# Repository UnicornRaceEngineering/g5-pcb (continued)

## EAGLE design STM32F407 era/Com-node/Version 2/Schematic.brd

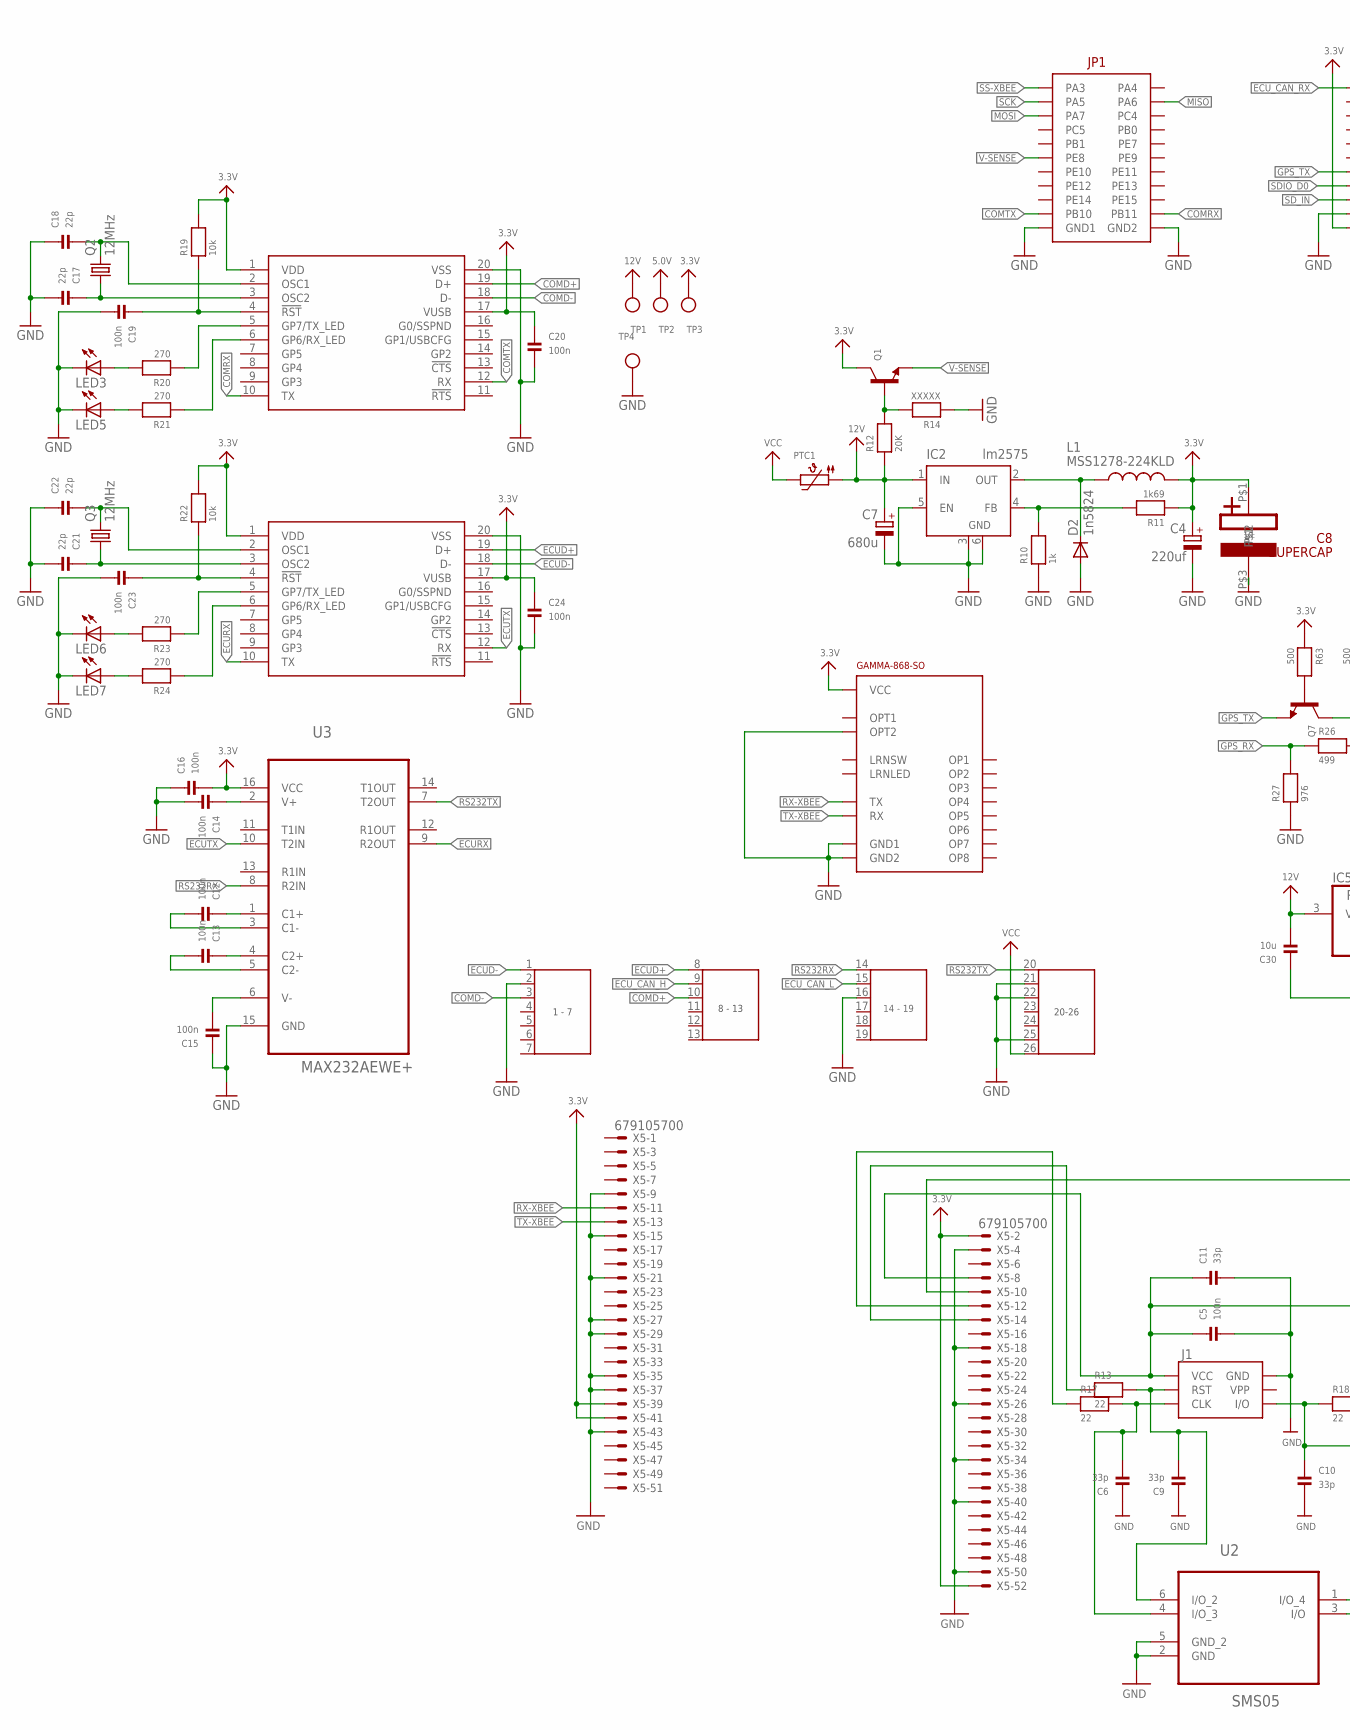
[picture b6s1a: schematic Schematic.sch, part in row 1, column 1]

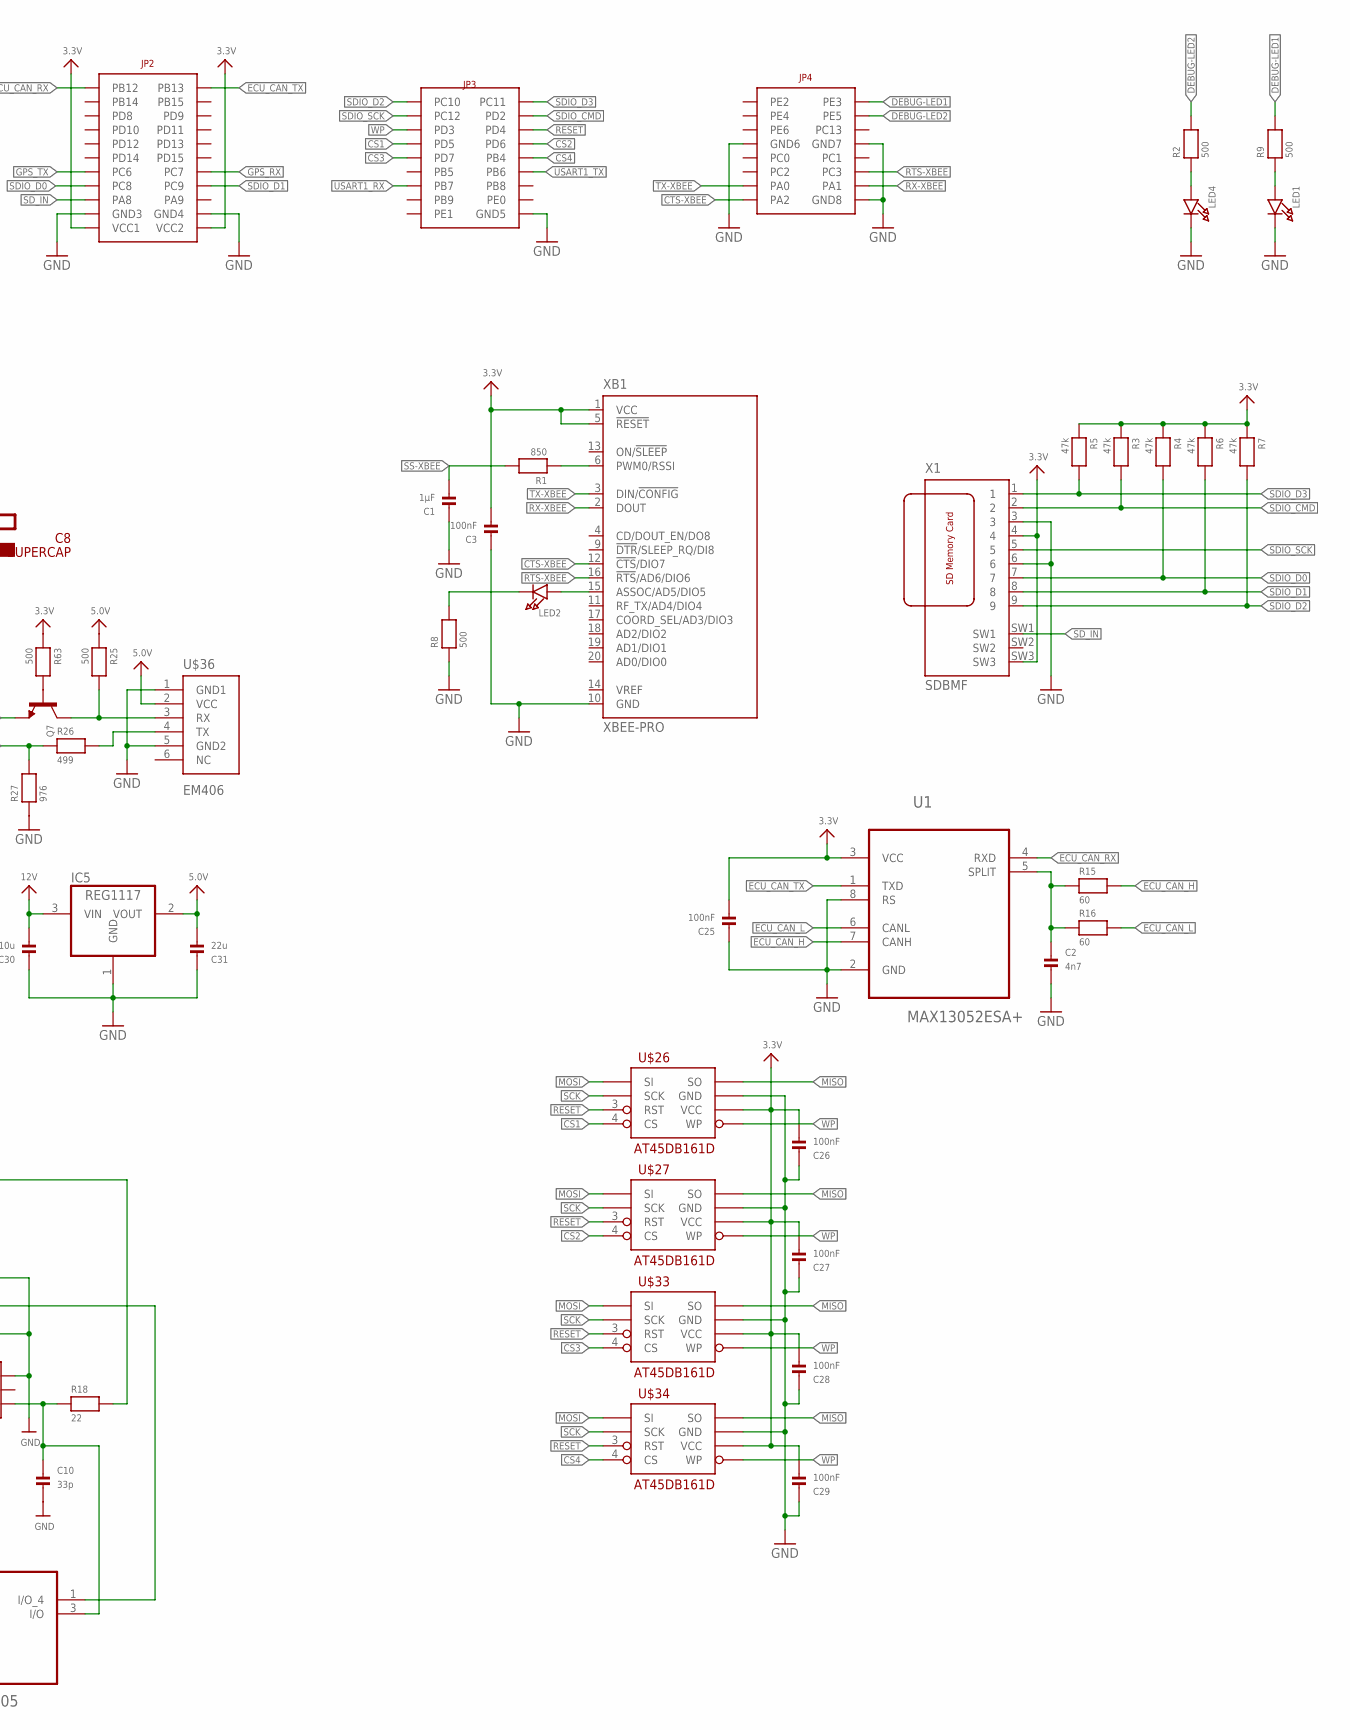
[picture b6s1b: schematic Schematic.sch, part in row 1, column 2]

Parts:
C1: 1µF; _0805
C2: 4n7; 0603
C3, C25, C26, C27, C28, C29: 100nF; _0603
C4: 220uf; E3,5-8
C5, C12, C13, C14, C15, C16, C19, C20, C23, C24: 100n; _0603
C6, C9, C10, C11: 33p; _0603
C7: 680u; E5-10,5
C8: SUPERCAP
C17, C18, C21, C22: 22p; _0603
C30: 10u; _0805
C31: 22u; _0805
D2: 1n5824; DO201-15
IC2: lm2575; TO263-5
IC5: REG1117; SOT223
J1: SIMHOLDERSIM; SIMHOLDER
L1: MSS1278-224KLD; CDRH125
LED1, LED2, LED4: LED1206; CHIPLED_1206
LED3, LED5, LED6, LED7: LEDCHIPLED_0805; CHIPLED_0805
PTC1: PTC1812
Q1, Q7: TRANSISTOR_NPNWIDE; SOT23-WIDE
Q2, Q3: 12MHz; HC49/S
R1: 850; _0603
R2, R8, R9, R25, R63: 500; _0603
R3, R4, R5, R6, R7: 47k; _0603
R10: 1k; _0603
R11: 1k69; _0603
R12: 20K; _0603
R13, R17, R18: 22; _0603
R14: XXXXX; _0603
R15, R16: 60; _0603
R19, R22: 10k; _0603
R20, R21, R23, R24: 270; _0603
R26: 499; _0603
R27: 976; _0603
TP1, TP2, TP3, TP4: TESTPOINT; TESTPOINT_SMT
U1: MAX13052ESA+; SOIC127P600X175-8N; MPN MAX13052ESA+
U2: SMS05; SOT95P280X145-6N
U3: MAX232AEWE+; SOIC127P1032X265-16N
U$1: CPU-BOARD; CPU-BOARD-JP1
U$18: SUPERSEAL-26
U$24, U$29: MCP2200; SO20L
U$26, U$27, U$33, U$34: AT45DB161D; SO08-EIAJ
U$32: GAMMA-868-SO; UNICORN_V2_GAMMA-868-SO
U$36: EM406
X1: SDBMF; SDBMF-009XXBXX2
X5: 679105700
XB1: XBEE-PRO

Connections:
3.3V: C3.2, C4.+, C8.P$1, C16.2, C20.1, C24.1, C25.2, C26.2, C27.2, C28.2, C29.2, L1.2, Q1.3 (C), R3.1, R4.1, R5.1, R6.1, R7.1, R11.1, R19.2, R22.2, R63.1, TP3.P$1, U1.3 (VCC), U3.16 (VCC), U$1.P$43 (VCC1), U$1.P$44 (VCC2), U$24.1 (VDD), U$24.17 (VUSB), U$26.6 (VCC), U$27.6 (VCC), U$29.1 (VDD), U$29.17 (VUSB), U$32.P$16 (VCC), U$33.6 (VCC), U$34.6 (VCC), X1.4, X1.SW3, X5.2, X5.39, X5.41, X5.52, XB1.1 (VCC), XB1.5 (!RESET)
5.0V: C31.2, IC5.2 (VOUT), R25.1, TP2.P$1, U$36.2 (VCC)
12V: C7.+, C30.2, IC2.1 (IN), IC5.3 (VIN), PTC1.P$1 (1), R12.1, TP1.P$1
COMD+: U$18.10, U$24.19 (D+)
COMD-: U$18.3, U$24.18 (D-)
COMRX: U$1.P$22 (PB11), U$24.10 (TX)
COMTX: U$1.P$21 (PB10), U$24.12 (RX)
CS1: U$1.P$51 (PD5), U$26.4 (CS)
CS2: U$1.P$52 (PD6), U$27.4 (CS)
CS3: U$1.P$53 (PD7), U$33.4 (CS)
CS4: U$1.P$54 (PB4), U$34.4 (CS)
CTS-XBEE: U$1.P$77 (PA2), XB1.12 (!CTS!/DIO7)
DEBUG-LED1: R9.2, U$1.P$64 (PE3)
DEBUG-LED2: R2.2, U$1.P$66 (PE5)
ECUD+: U$18.8, U$29.19 (D+)
ECUD-: U$18.1, U$29.18 (D-)
ECURX: U3.9 (R2OUT), U$29.10 (TX)
ECUTX: U3.10 (T2IN), U$29.12 (RX)
ECU_CAN_H: R15.2, U1.7 (CANH), U$18.9
ECU_CAN_L: R16.2, U1.6 (CANL), U$18.15
ECU_CAN_RX: U1.4 (RXD), U$1.P$23 (PB12)
ECU_CAN_TX: U1.1 (TXD), U$1.P$24 (PB13)
GND: C1.1, C2.2, C3.1, C4.-, C5.2, C6.1, C7.-, C8.P$3, C9.1, C10.2, C11.2, C14.2, C15.1, C16.1, C17.2, C18.1, C19.2, C20.2, C21.2, C22.1, C23.2, C24.2, C25.1, C26.1, C27.1, C28.1, C29.1, C30.1, C31.1, D2.A, IC2.3 (GND), IC2.5 (EN), IC2.6 (GND), IC5.1 (GND), J1.C5 (GND), LED1.C, LED3.C, LED4.C, LED5.C, LED6.C, LED7.C, R8.1, R10.1, R14.1, R27.1, TP4.P$1, U1.2 (GND), U1.8 (RS), U2.2 (GND), U2.5 (GND_2), U3.15 (GND), U$1.P$19 (GND1), U$1.P$20 (GND2), U$1.P$41 (GND3), U$1.P$42 (GND4), U$1.P$62 (GND5), U$1.P$69 (GND6), U$1.P$70 (GND7), U$1.P$78 (GND8), U$18.2, U$18.16, U$18.21, U$18.22, U$18.25, U$24.20 (VSS), U$26.7 (GND), U$27.7 (GND), U$29.20 (VSS), U$32.P$2 (GND1), U$32.P$14 (OPT2), U$32.P$15 (GND2), U$33.7 (GND), U$34.7 (GND), U$36.1 (GND1), U$36.5 (GND2), X1.3, X1.6, X5.4, X5.9, X5.15, X5.18, X5.21, X5.26, X5.27, X5.29, X5.34, X5.35, X5.37, X5.40, X5.43, X5.50, XB1.10 (GND)
GPS_RX: R26.1, R27.2, U$1.P$36 (PC7)
GPS_TX: Q7.2 (E), U$1.P$35 (PC6)
MISO: U$1.P$4 (PA6), U$26.8 (SO), U$27.8 (SO), U$33.8 (SO), U$34.8 (SO)
MOSI: U$1.P$5 (PA7), U$26.1 (SI), U$27.1 (SI), U$33.1 (SI), U$34.1 (SI)
unnamed: IC2.4 (FB), R10.2, R11.2
unnamed: R1.1, XB1.6 (PWM0/RSSI)
unnamed: LED4.A, R2.1
unnamed: D2.C, IC2.2 (OUT), L1.1
unnamed: LED2.A, XB1.15 (ASSOC/AD5/DIO5)
unnamed: LED2.C, R8.2
unnamed: LED1.A, R9.1
unnamed: C13.1, U3.4 (C2+)
unnamed: C12.2, U3.3 (C1-)
unnamed: C12.1, U3.1 (C1+)
unnamed: C15.2, U3.6 (V-)
unnamed: Q1.1 (B), R12.2, R14.2
unnamed: C14.1, U3.2 (V+)
unnamed: C9.2, J1.C2 (RST), R13.2, U2.6 (I/O_2)
unnamed: C6.2, J1.C3 (CLK), R17.2, U2.4 (I/O_3)
unnamed: C10.1, J1.C7 (I/O), R18.1, U2.3 (I/O)
unnamed: C5.1, C11.1, J1.C1 (VCC), U2.1 (I/O_4), X5.8
unnamed: C13.2, U3.5 (C2-)
unnamed: C2.1, R15.1, R16.1, U1.5 (SPLIT)
unnamed: R18.2, X5.10
unnamed: R13.1, X5.14
unnamed: R17.1, X5.12
unnamed: C22.2, Q3.2, U$29.2 (OSC1)
unnamed: C18.2, Q2.2, U$24.2 (OSC1)
unnamed: C17.1, Q2.1, U$24.3 (OSC2)
unnamed: C21.1, Q3.1, U$29.3 (OSC2)
unnamed: R21.1, U$24.6 (GP6/RX_LED)
unnamed: R20.1, U$24.5 (GP7/TX_LED)
unnamed: C19.1, R19.1, U$24.4 (!RST)
unnamed: R24.1, U$29.6 (GP6/RX_LED)
unnamed: R23.1, U$29.5 (GP7/TX_LED)
unnamed: LED3.A, R20.2
unnamed: LED5.A, R21.2
unnamed: C23.1, R22.1, U$29.4 (!RST)
unnamed: LED6.A, R23.2
unnamed: LED7.A, R24.2
unnamed: Q7.1 (B), R63.2
RESET: U$1.P$50 (PD4), U$26.3 (RST), U$27.3 (RST), U$33.3 (RST), U$34.3 (RST)
RS232RX: U3.8 (R2IN), U$18.14
RS232TX: U3.7 (T2OUT), U$18.20
RTS-XBEE: U$1.P$74 (PC3), XB1.16 (!RTS!/AD6/DIO6)
RX-XBEE: U$1.P$76 (PA1), U$32.P$17 (TX), X5.11, XB1.2 (DOUT)
RXD1: R26.2, U$36.4 (TX)
SCK: U$1.P$3 (PA5), U$26.2 (SCK), U$27.2 (SCK), U$33.2 (SCK), U$34.2 (SCK)
SDIO_CMD: R3.2, U$1.P$48 (PD2), X1.2
SDIO_D0: R4.2, U$1.P$37 (PC8), X1.7
SDIO_D1: R6.2, U$1.P$38 (PC9), X1.8
SDIO_D2: R7.2, U$1.P$45 (PC10), X1.9
SDIO_D3: R5.2, U$1.P$46 (PC11), X1.1
SDIO_SCK: U$1.P$47 (PC12), X1.5
SD_IN: U$1.P$39 (PA8), X1.SW1
SS-XBEE: C1.2, R1.2, U$1.P$1 (PA3)
TX-XBEE: U$1.P$75 (PA0), U$32.P$18 (RX), X5.13, XB1.3 (DIN/!CONFIG)
TXD1: Q7.3 (C), R25.2, U$36.3 (RX)
USART1_RX: U$1.P$57 (PB7)
USART1_TX: U$1.P$56 (PB6)
V-SENSE: Q1.2 (E), U$1.P$11 (PE8)
VCC: PTC1.P$2 (2), U$18.26
WP: U$1.P$49 (PD3), U$26.5 (WP), U$27.5 (WP), U$33.5 (WP), U$34.5 (WP)

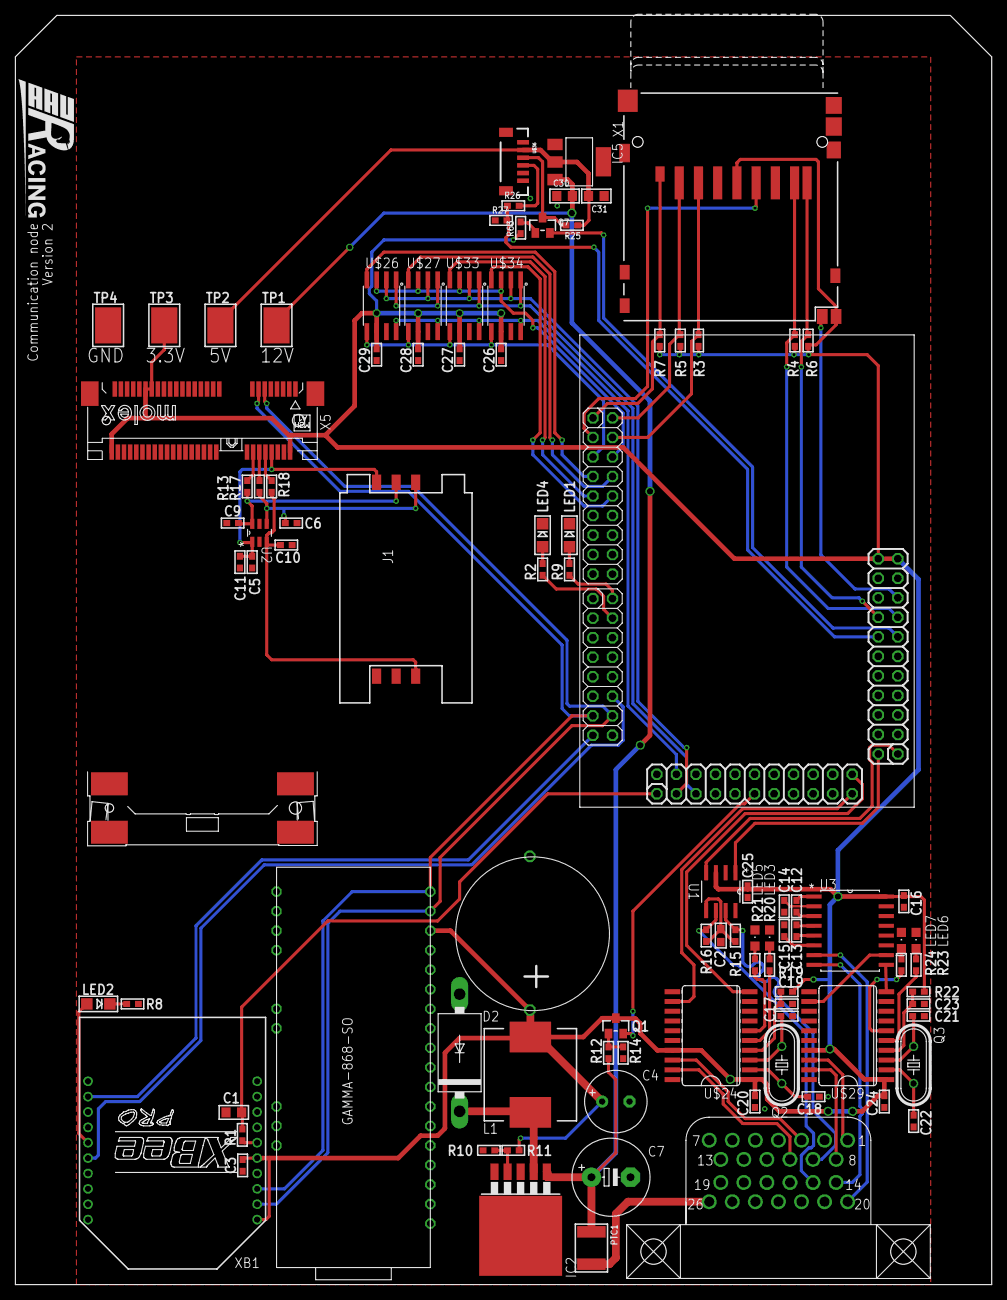
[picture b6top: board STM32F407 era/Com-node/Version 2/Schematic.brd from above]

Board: 2 copper layers, 127.0 x 165.1 mm, 96 parts (0 on the bottom side), 84 nets.

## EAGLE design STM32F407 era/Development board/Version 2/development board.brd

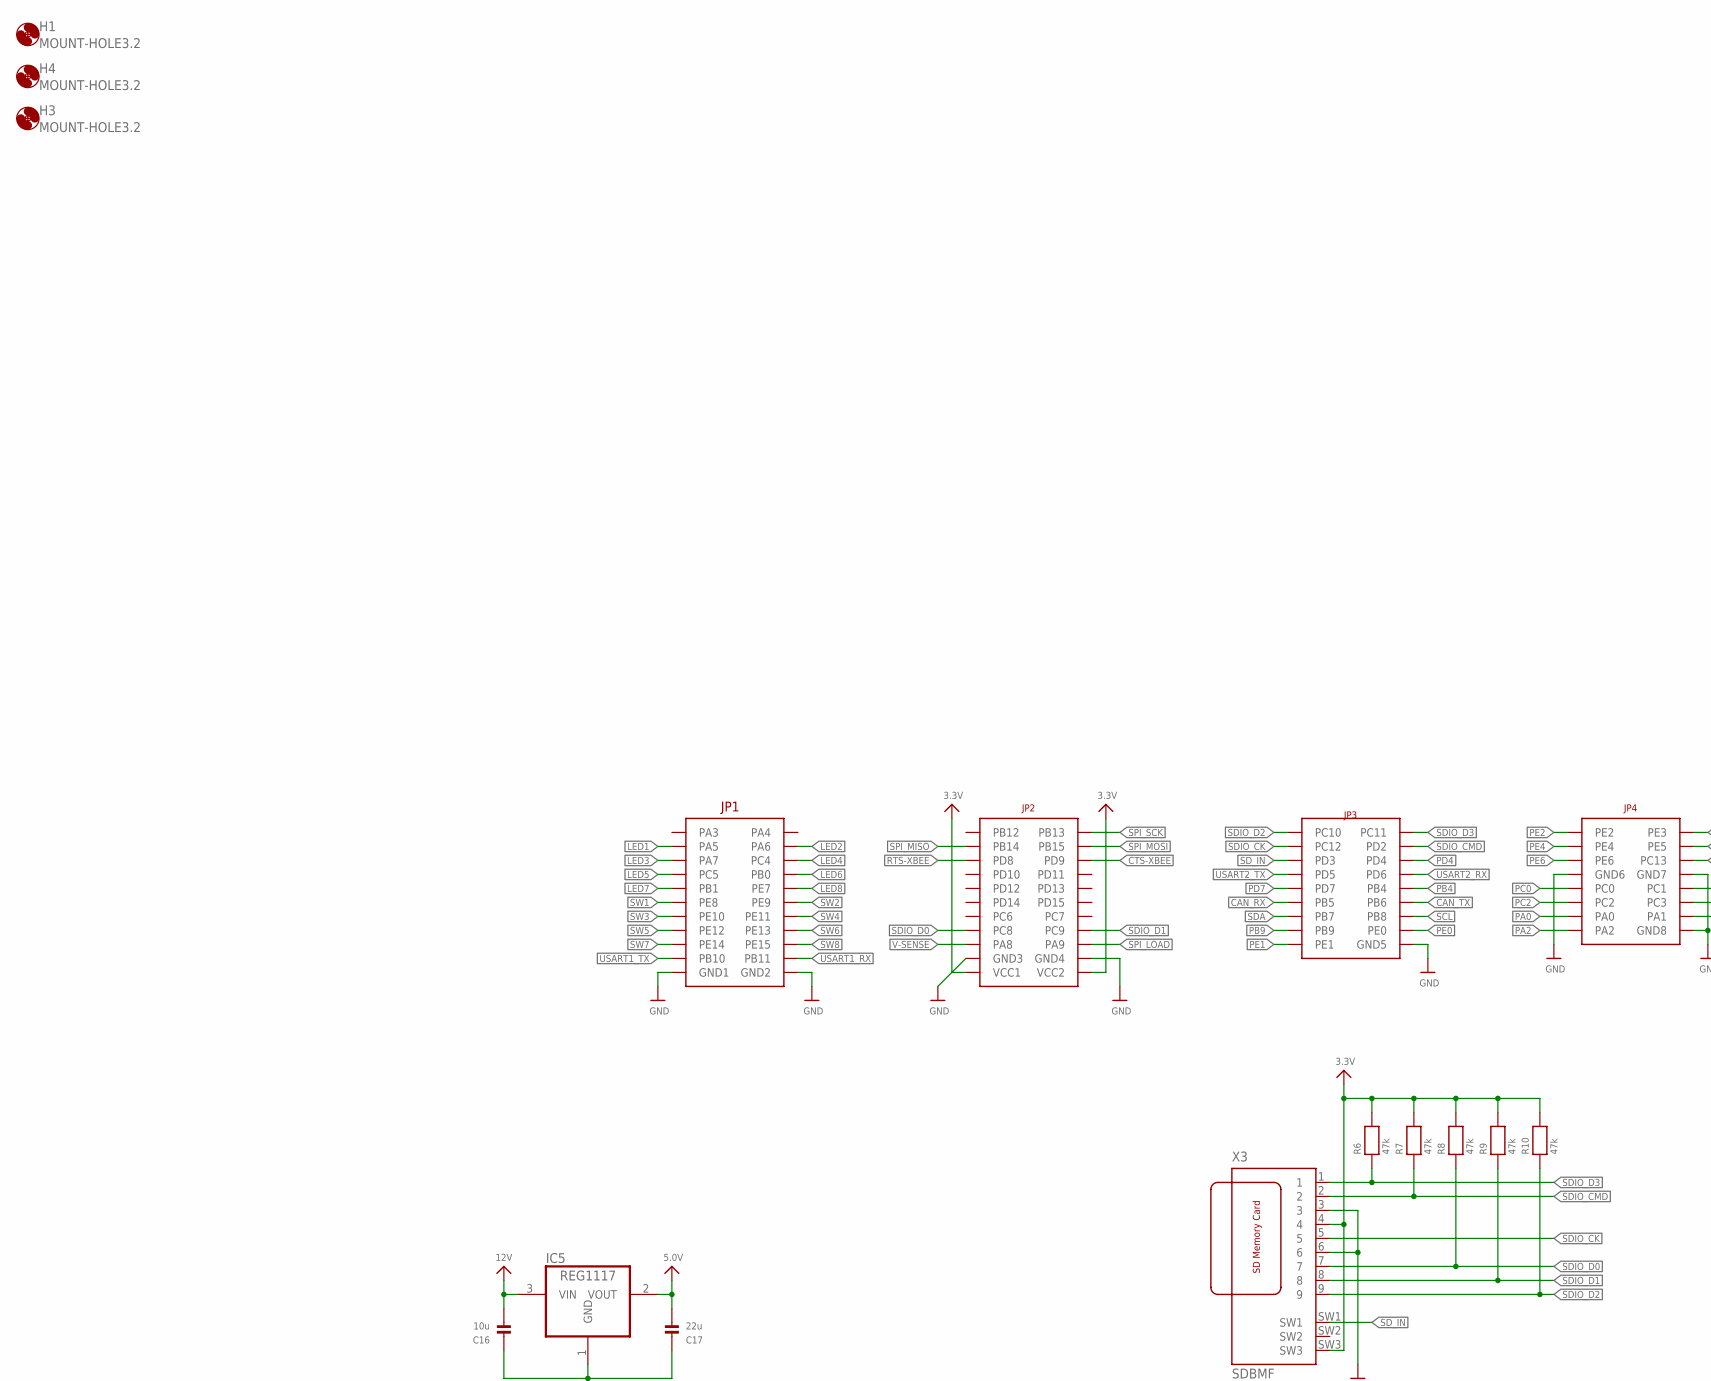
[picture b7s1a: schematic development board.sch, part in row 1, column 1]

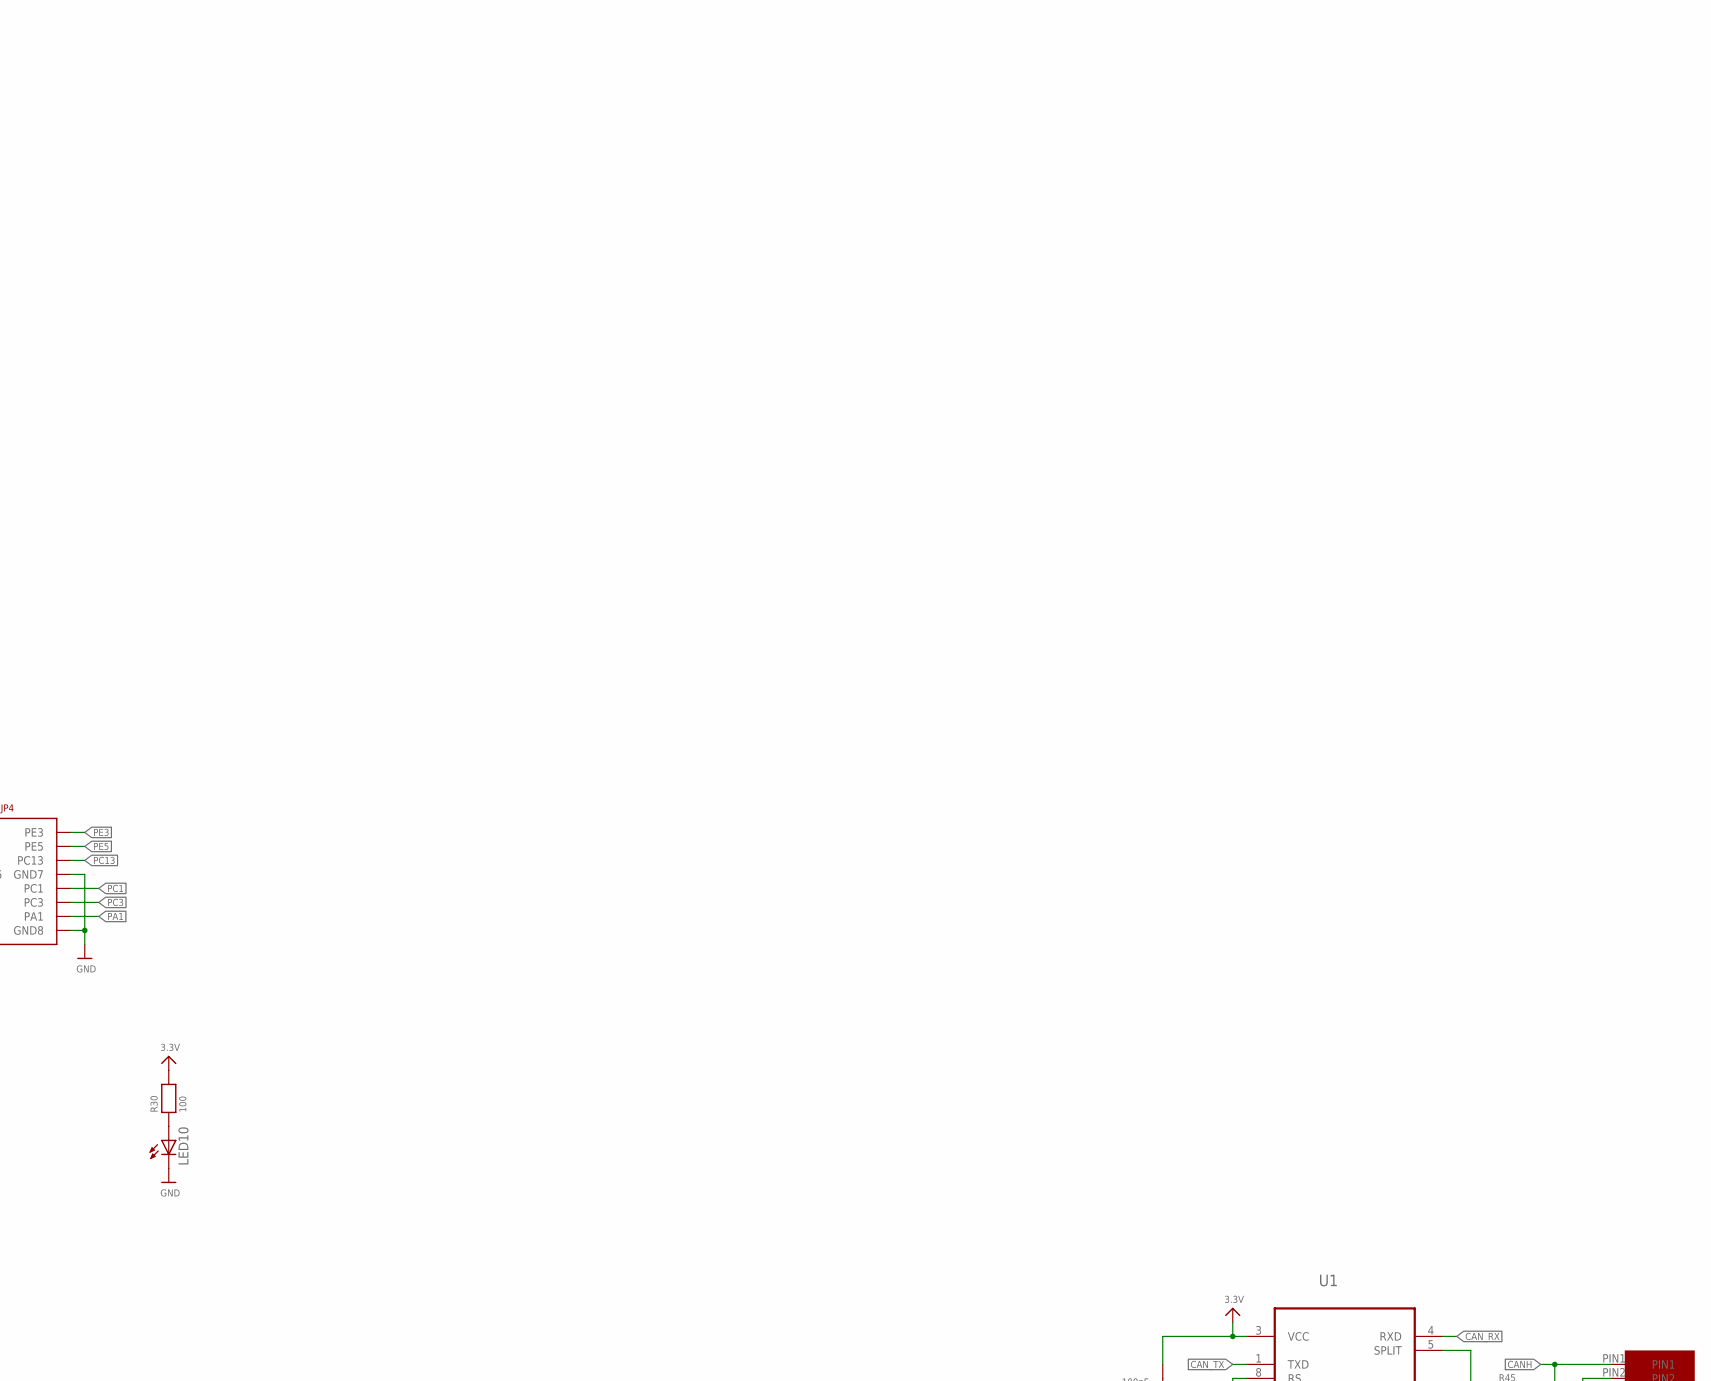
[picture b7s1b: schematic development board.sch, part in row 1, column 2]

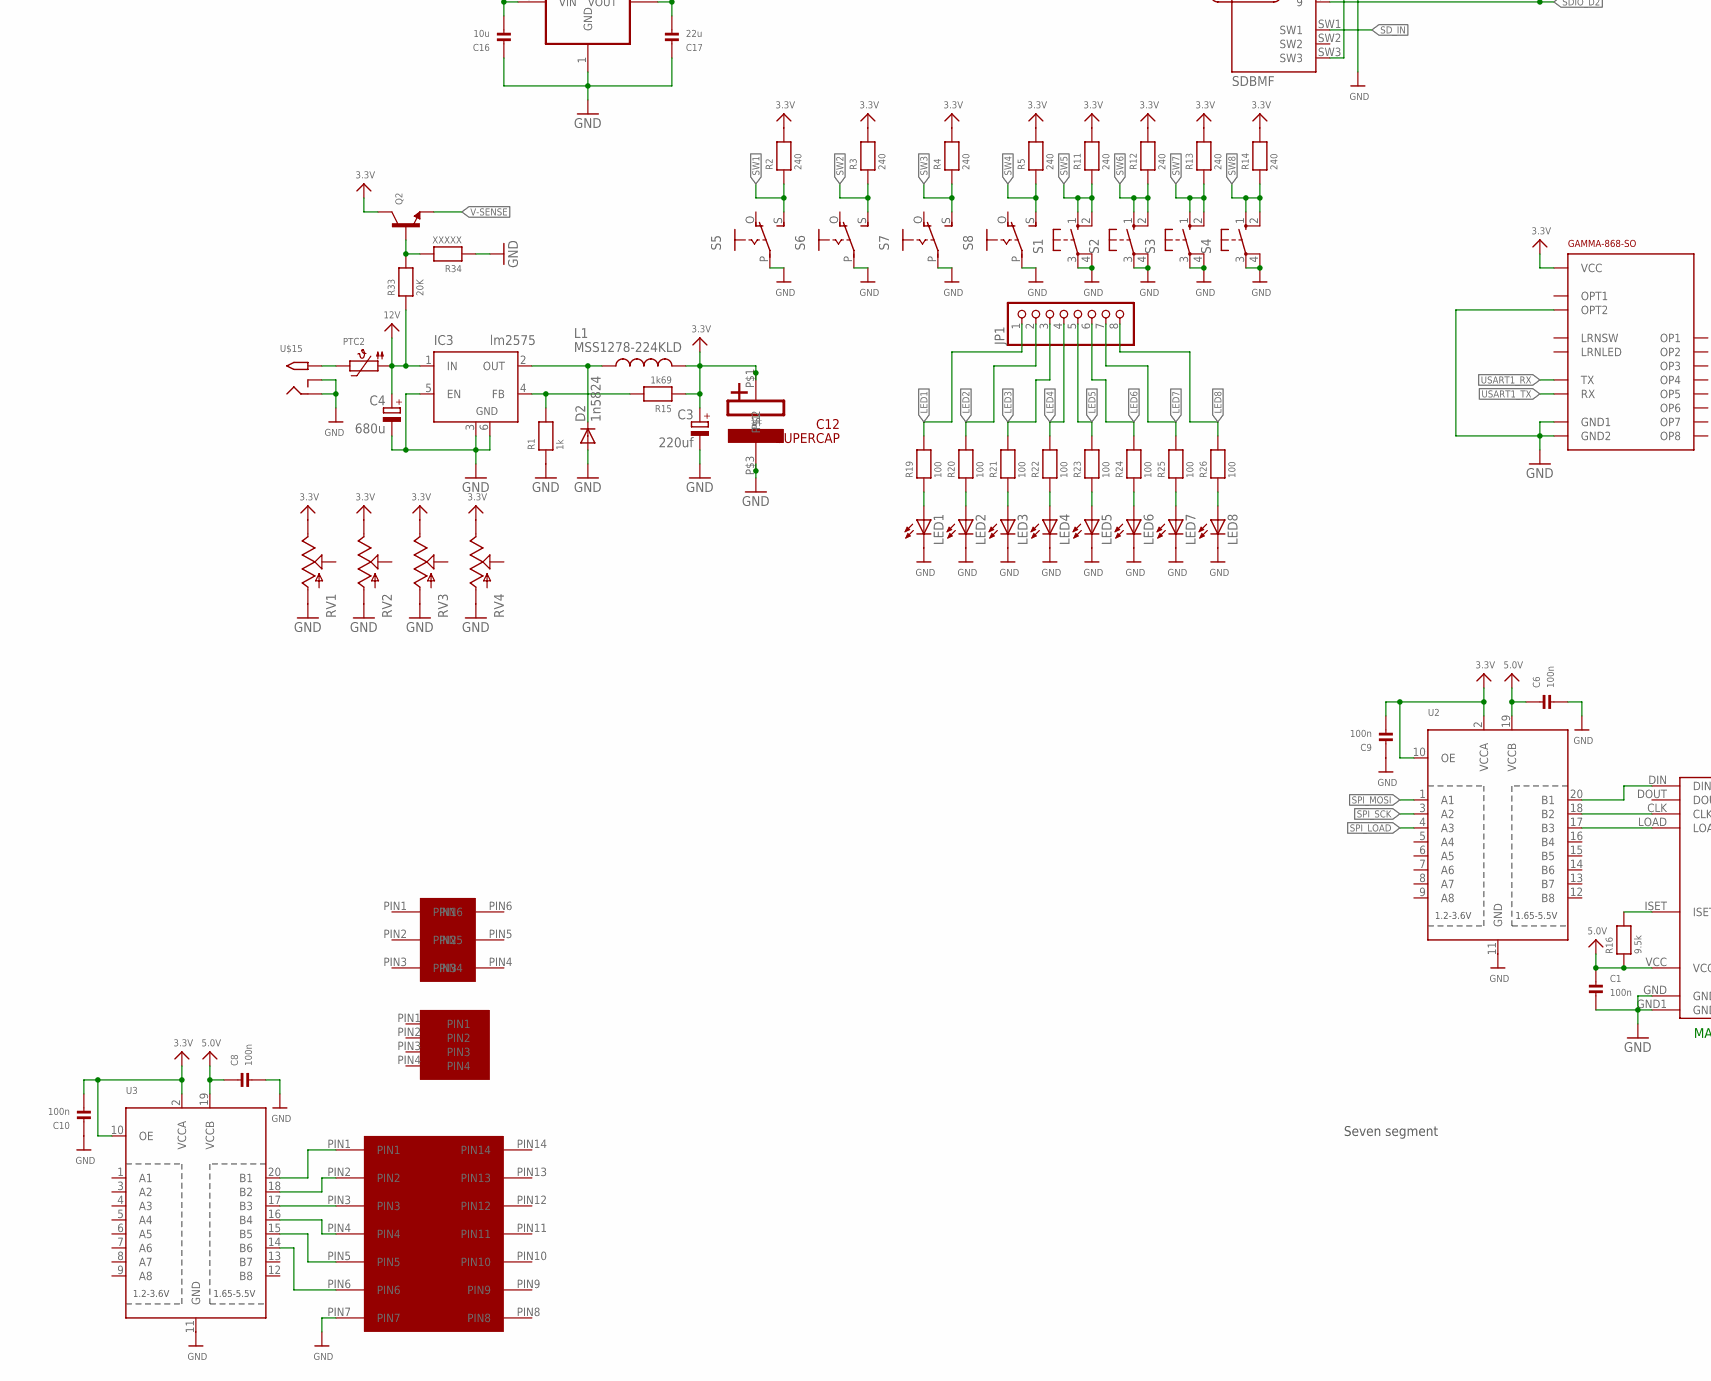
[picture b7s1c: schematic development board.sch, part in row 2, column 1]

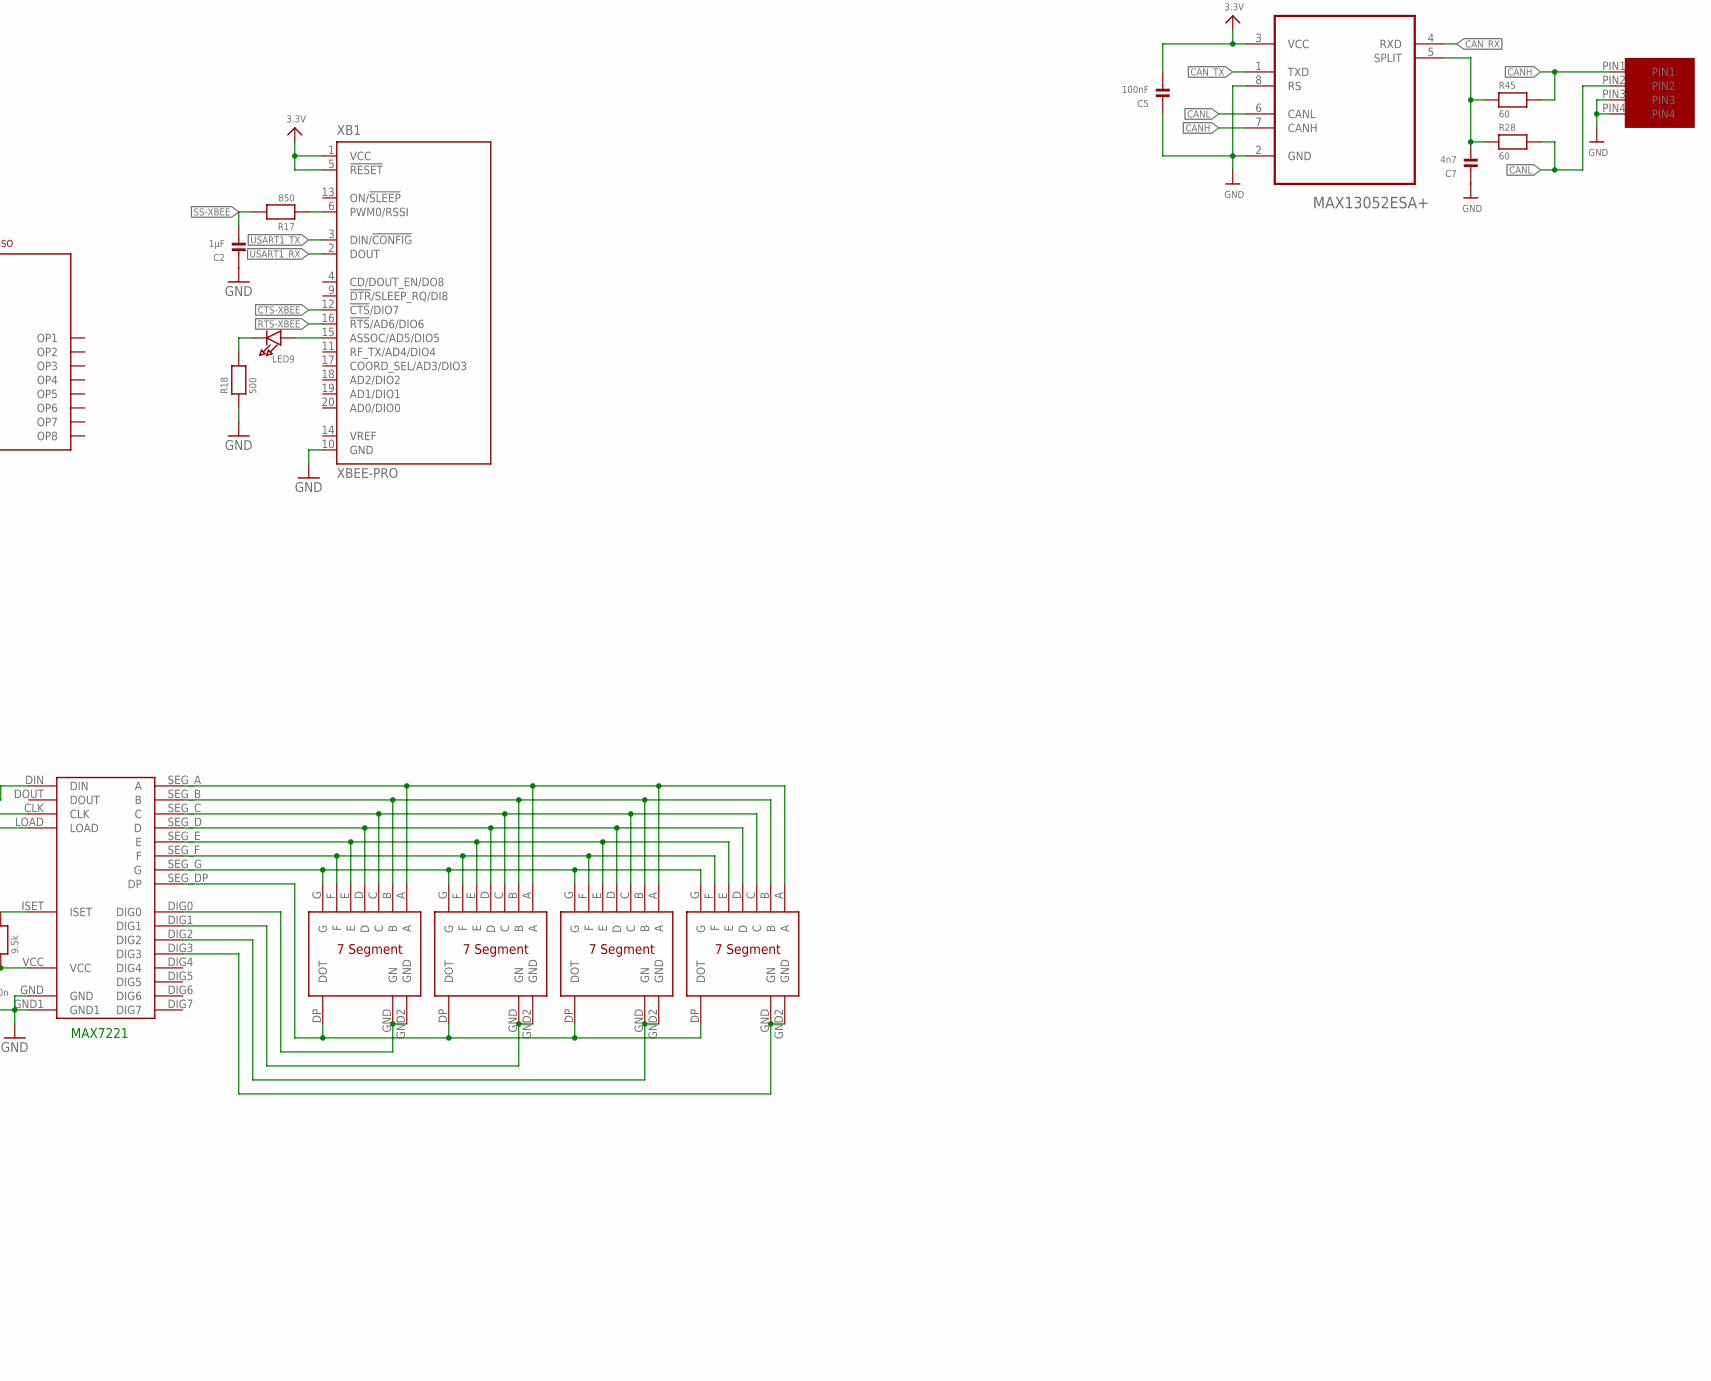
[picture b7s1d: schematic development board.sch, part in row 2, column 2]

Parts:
C1, C6, C8, C9, C10: 100n; _0603
C2: 1µF; _0805
C3: 220uf; E3,5-8
C4: 680u; E5-10,5
C5: 100nF; _0603
C7: 4n7; _0603
C12: SUPERCAP
C16: 10u; _0805
C17: 22u; _0805
D2: 1n5824; DO201-15
H1, H3, H4: MOUNT-HOLE3.2; 3,2
IC3: lm2575; TO263-5
IC5: REG1117; SOT223
JP1: PINHD-1X8BIG; 1X08-BIG
L1: MSS1278-224KLD; CDRH125
LED1, LED2, LED3, LED4, LED5, LED6, LED7, LED8, LED10: LEDCHIPLED_1206; CHIPLED_1206
LED9: LED1206; CHIPLED_1206
MAX7221: MAX7221-SMD; MAX7221
PTC2: PTC1812
Q2: TRANSISTOR_NPNWIDE; SOT23-WIDE
R1: 1k; _0603
R2, R3, R4, R5, R11, R12, R13, R14: 240; _0603
R6, R7, R8, R9, R10: 47k; _0603
R15: 1k69; _0603
R16: 9.5k; _0603
R17: 850; _0603
R18: 500; _0603
R19, R20, R21, R22, R23, R24, R25, R26, R30: 100; _0603
R28, R45: 60; _0603
R33: 20K; _0603
R34: XXXXX; _0603
RV1, RV2, RV3, RV4: POT; ALPS_POT
S1, S2, S3, S4: 10-XX; B3F-10XX; MPN B3F-1000
S5, S6, S7, S8: EG1218S; EG1218
U1: MAX13052ESA+; SOIC127P600X175-8N
U2, U3: TXB0108PWR; TSSOP20
U$1: CPU-BOARD; CPU-BOARD-JP1
U$2: GAMMA-868-SO; UNICORN_V2_GAMMA-868-SO
U$15: 2.1MMJACKSMT; DCJACK_2MM_SMT
U$23, U$24, U$25, U$26: REDSEVENSEGMENT; REDSEGMENT
U$57, U$67: MICROFIT4; MICROFIT4SOCK
U$61: MICROFIT14; MICROFIT14SOCK
U$68: MICROFIT6; MICROFIT6SOCK
X3: SDBMF; SDBMF-009XXBXX2
XB1: XBEE-PRO

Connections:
3.3V: C3.+, C5.2, C9.2, C10.2, C12.P$1, L1.2, Q2.3 (C), R2.2, R3.2, R4.2, R5.2, R6.2, R7.2, R8.2, R9.2, R10.2, R11.2, R12.2, R13.2, R14.2, R15.1, R30.2, RV1.P$1 (E), RV2.P$1 (E), RV3.P$1 (E), RV4.P$1 (E), U1.3 (VCC), U2.2 (VCCA), U2.10 (OE), U3.2 (VCCA), U3.10 (OE), U$1.P$43 (VCC1), U$1.P$44 (VCC2), U$2.P$16 (VCC), X3.4, X3.SW3, XB1.1 (VCC), XB1.5 (!RESET)
5.0V: C1.1, C6.1, C8.1, C17.2, IC5.2 (VOUT), MAX7221.VCC, R16.1, U2.19 (VCCB), U3.19 (VCCB)
12V: C4.+, C16.2, IC3.1 (IN), IC5.3 (VIN), PTC2.P$1 (1), R33.1
CANH: R45.2, U1.7 (CANH), U$57.PIN1
CANL: R28.2, U1.6 (CANL), U$57.PIN2
CAN_RX: U1.4 (RXD), U$1.P$55 (PB5)
CAN_TX: U1.1 (TXD), U$1.P$56 (PB6)
CTS-XBEE: U$1.P$28 (PD9), XB1.12 (!CTS!/DIO7)
DIG0: MAX7221.DIG0, U$23.GND (GN), U$23.GND2 (GND)
DIG1: MAX7221.DIG1, U$24.GND (GN), U$24.GND2 (GND)
DIG2: MAX7221.DIG2, U$25.GND (GN), U$25.GND2 (GND)
DIG3: MAX7221.DIG3, U$26.GND (GN), U$26.GND2 (GND)
GND: C1.2, C2.1, C3.-, C4.-, C5.1, C6.2, C7.1, C8.2, C9.1, C10.1, C12.P$3, C16.1, C17.1, D2.A, IC3.3 (GND), IC3.5 (EN), IC3.6 (GND), IC5.1 (GND), LED1.C, LED2.C, LED3.C, LED4.C, LED5.C, LED6.C, LED7.C, LED8.C, LED10.C, MAX7221.GND, MAX7221.GND1, R1.1, R18.1, R34.1, RV1.P$3 (A), RV2.P$3 (A), RV3.P$3 (A), RV4.P$3 (A), S1.3, S1.4 (P1), S2.3, S2.4 (P1), S3.3, S3.4 (P1), S4.3, S4.4 (P1), S5.P, S6.P, S7.P, S8.P, U1.2 (GND), U1.8 (RS), U2.11 (GND), U3.11 (GND), U$1.P$19 (GND1), U$1.P$20 (GND2), U$1.P$41 (GND3), U$1.P$42 (GND4), U$1.P$62 (GND5), U$1.P$69 (GND6), U$1.P$70 (GND7), U$1.P$78 (GND8), U$2.P$2 (GND1), U$2.P$14 (OPT2), U$2.P$15 (GND2), U$15.GND (RING), U$15.GNDBREAK (RING_SW), U$57.PIN3, U$57.PIN4, U$61.PIN7, X3.3, X3.6, XB1.10 (GND); also elsewhere on the board
LED1: JP1.1, R19.2, U$1.P$3 (PA5)
LED2: JP1.2, R20.2, U$1.P$4 (PA6)
LED3: JP1.3, R21.2, U$1.P$5 (PA7)
LED4: JP1.4, R22.2, U$1.P$6 (PC4)
LED5: JP1.5, R23.2, U$1.P$7 (PC5)
LED6: JP1.6, R24.2, U$1.P$8 (PB0)
LED7: JP1.7, R25.2, U$1.P$9 (PB1)
LED8: JP1.8, R26.2, U$1.P$10 (PE7)
unnamed: PTC2.P$2 (2), U$15.PWR2 (TIP)
unnamed: R17.1, XB1.6 (PWM0/RSSI)
unnamed: U3.17 (B3), U$61.PIN3
unnamed: U3.16 (B4), U$61.PIN4
unnamed: LED9.A, XB1.15 (ASSOC/AD5/DIO5)
unnamed: LED9.C, R18.2
unnamed: Q2.1 (B), R33.2, R34.2
unnamed: U3.18 (B2), U$61.PIN2
unnamed: U3.20 (B1), U$61.PIN1
unnamed: U3.15 (B5), U$61.PIN5
unnamed: U3.14 (B6), U$61.PIN6
unnamed: MAX7221.SEG_A (A), U$23.A, U$24.A, U$25.A, U$26.A
unnamed: IC3.4 (FB), R1.2, R15.2
unnamed: LED10.A, R30.1
unnamed 35: D2.C, IC3.2 (OUT), L1.1; also elsewhere on the board
unnamed: MAX7221.SEG_B (B), U$23.B, U$24.B, U$25.B, U$26.B
unnamed: MAX7221.SEG_C (C), U$23.C, U$24.C, U$25.C, U$26.C
unnamed: MAX7221.SEG_D (D), U$23.D, U$24.D, U$25.D, U$26.D
unnamed: MAX7221.SEG_E (E), U$23.E, U$24.E, U$25.E, U$26.E
unnamed: MAX7221.SEG_F (F), U$23.F, U$24.F, U$25.F, U$26.F
unnamed: MAX7221.SEG_G (G), U$23.G, U$24.G, U$25.G, U$26.G
unnamed: LED1.A, R19.1
unnamed: LED2.A, R20.1
unnamed: LED3.A, R21.1
unnamed: LED4.A, R22.1
unnamed: LED5.A, R23.1
unnamed: LED6.A, R24.1
unnamed: LED7.A, R25.1
unnamed: LED8.A, R26.1
unnamed: MAX7221.SEG_DP (DP), U$23.DP (DOT), U$24.DP (DOT), U$25.DP (DOT), U$26.DP (DOT)
unnamed: MAX7221.ISET, R16.2
unnamed: MAX7221.CLK, U2.18 (B2)
unnamed: MAX7221.LOAD, U2.17 (B3)
unnamed: MAX7221.DIN, U2.20 (B1)
unnamed: C7.2, R28.1, R45.1, U1.5 (SPLIT)
PA0: U$1.P$75 (PA0)
PA1: U$1.P$76 (PA1)
PA2: U$1.P$77 (PA2)
PB4: U$1.P$54 (PB4)
PB9: U$1.P$59 (PB9)
PC0: U$1.P$71 (PC0)
PC1: U$1.P$72 (PC1)
PC2: U$1.P$73 (PC2)
PC3: U$1.P$74 (PC3)
PC13: U$1.P$68 (PC13)
PD4: U$1.P$50 (PD4)
PD7: U$1.P$53 (PD7)
PE0: U$1.P$60 (PE0)
PE1: U$1.P$61 (PE1)
PE2: U$1.P$63 (PE2)
PE3: U$1.P$64 (PE3)
PE4: U$1.P$65 (PE4)
PE5: U$1.P$66 (PE5)
PE6: U$1.P$67 (PE6)
RTS-XBEE: U$1.P$27 (PD8), XB1.16 (!RTS!/AD6/DIO6)
SCL: U$1.P$58 (PB8)
SDA: U$1.P$57 (PB7)
SDIO_CK: U$1.P$47 (PC12), X3.5
SDIO_CMD: R7.1, U$1.P$48 (PD2), X3.2
SDIO_D0: R8.1, U$1.P$37 (PC8), X3.7
SDIO_D1: R9.1, U$1.P$38 (PC9), X3.8
SDIO_D2: R10.1, U$1.P$45 (PC10), X3.9
SDIO_D3: R6.1, U$1.P$46 (PC11), X3.1
SD_IN: U$1.P$49 (PD3), X3.SW1
SPI_LOAD: U2.4 (A3), U$1.P$40 (PA9)
SPI_MISO: U$1.P$25 (PB14)
SPI_MOSI: U2.1 (A1), U$1.P$26 (PB15)
SPI_SCK: U2.3 (A2), U$1.P$24 (PB13)
SS-XBEE: C2.2, R17.2
SW1: R2.1, S5.S, U$1.P$11 (PE8)
SW2: R3.1, S6.S, U$1.P$12 (PE9)
SW3: R4.1, S7.S, U$1.P$13 (PE10)
SW4: R5.1, S8.S, U$1.P$14 (PE11)
SW5: R11.1, S1.1 (S), S1.2 (S1), U$1.P$15 (PE12)
SW6: R12.1, S2.1 (S), S2.2 (S1), U$1.P$16 (PE13)
SW7: R13.1, S3.1 (S), S3.2 (S1), U$1.P$17 (PE14)
SW8: R14.1, S4.1 (S), S4.2 (S1), U$1.P$18 (PE15)
USART1_RX: U$1.P$22 (PB11), U$2.P$17 (TX), XB1.2 (DOUT)
USART1_TX: U$1.P$21 (PB10), U$2.P$18 (RX), XB1.3 (DIN/!CONFIG)
USART2_RX: U$1.P$52 (PD6)
USART2_TX: U$1.P$51 (PD5)
V-SENSE: Q2.2 (E), U$1.P$39 (PA8)

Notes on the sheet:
MAX7221
Seven segment
